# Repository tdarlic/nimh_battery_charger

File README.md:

# NiMh Battery Charger for 4 AA/AAA batteries

Idea taken from BigClive:
[https://www.reddit.com/r/BigCliveDotCom/comments/tcny85/simple_nimh_battery_charger_with_pcb_files/]

In order to know when the batteries might be charged my plan was to use the timer and a LED. 
I need a 24 hour timer and 555 adds more complications and cannot have 24 hours delays.
Then I tried to get a more modern timer solution but at the end it's much cheaper to use cheap MCU.
That seems wastefull to use MCU only as a timer so I'll ad some fluff to it and maybe connect more batteries to one.

For detecting battery and the timers used ch32v003fun:
[https://github.com/cnlohr/ch32v003fun?tab=readme-ov-file]

Example of the dev board:
[https://oshwlab.com/wagiminator/ch32v003f4p6-development-board]

Development board github:
[https://github.com/wuxx/nanoCH32V003]

To use the WCH-LinkE on Linux, you need to grant access permissions beforehand by executing the following commands:

```shell
echo 'SUBSYSTEM=="usb", ATTR{idVendor}=="1a86", ATTR{idProduct}=="8010", MODE="666"' | sudo tee /etc/udev/rules.d/99-WCH-LinkE.rules
echo 'SUBSYSTEM=="usb", ATTR{idVendor}=="1a86", ATTR{idProduct}=="8012", MODE="666"' | sudo tee -a /etc/udev/rules.d/99-WCH-LinkE.rules
sudo udevadm control --reload-rules

```

To upload firmware and perform debugging, you need to ensure that the development board is disconnected from any power sources. Then, you should make the following connections to the WCH-LinkE:
```
| WCH-LinkE |      | DevBoard |
|-----------|------|----------|
|  SWDIO    | <--> |DIO       |
|    3V3    | ---> |3V3       |
|    GND    | ---> |GND       |

```
## NRST [D7] pin AS GPIO
Must be configured to be GPIO and not NRST pin
```shell
./minichlink -D
```
New make command was added to do this
```shell
make nrstoff
```

## Quick reference

## Dev board pinout

## Dev board schematic

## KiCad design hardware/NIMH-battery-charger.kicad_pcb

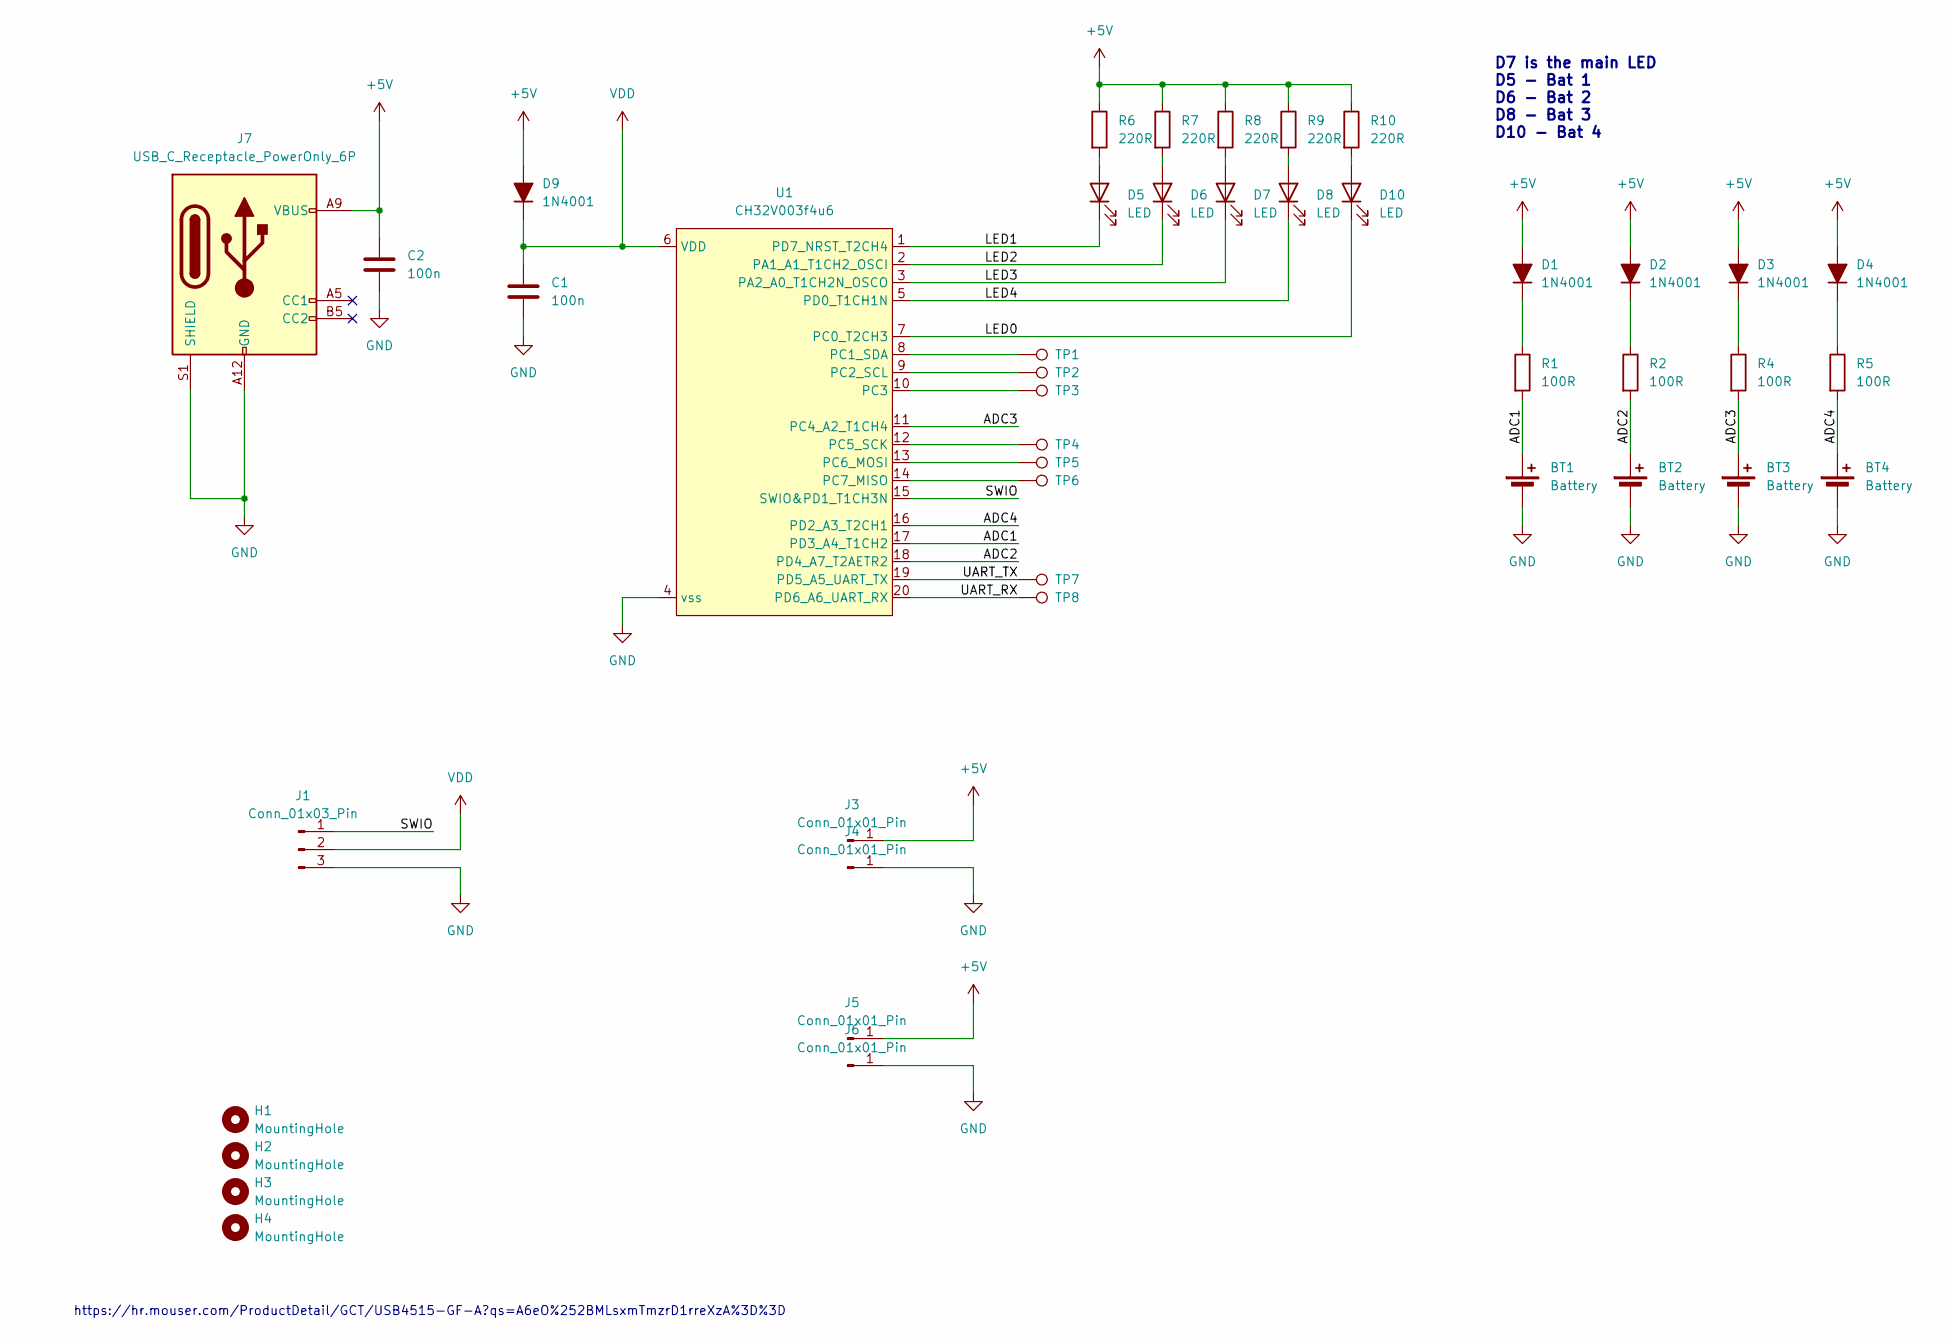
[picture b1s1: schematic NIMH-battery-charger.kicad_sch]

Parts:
BT1, BT2, BT3, BT4: Battery; UM-3X1-AA
C1, C2: 100n; C_0805_2012Metric_Pad1.18x1.45mm
D1, D2, D3, D4, D9: 1N4001; D_SOD-323_BigPads
D5, D6, D7, D8, D10: LED; LED_1206_3216Metric_ReverseMount_Hole1.8x2.4mm
H1, H2, H3, H4: MountingHole; MountingHole_3.2mm_M3_ISO14580_Pad_TopOnly
J1: Conn_01x03_Pin; Harwin_M20-89003xx_1x03_P2.54mm_Horizontal
J3, J4, J5, J6: Conn_01x01_Pin; PAD
J7: USB_C_Receptacle_PowerOnly_6P; USB4515-GF-A
R1, R2, R4, R5: 100R; R_0805_2012Metric_Pad1.20x1.40mm_HandSolder
R6, R7, R8, R9, R10: 220R; R_0805_2012Metric_Pad1.20x1.40mm_HandSolder
TP1, TP2, TP3, TP4, TP5, TP6, TP7, TP8: TestPoint; TestPoint_Pad_D1.5mm
U1: CH32V003f4u6; QFN-20-1EP_3x3mm_P0.4mm_EP1.65x1.65mm

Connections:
+5V: C2.1, D1.2 (A), D2.2 (A), D3.2 (A), D4.2 (A), D9.2 (A), J3.1, J5.1, J7.A9 (VBUS), J7.B9 (VBUS), R6.1, R7.1, R8.1, R9.1, R10.1
/ADC1: BT1.1 (+), R1.2, U1.17 (PD2_A4_T1CH2)
/ADC2: BT2.1 (+), R2.2, U1.18 (PD4_A7_T2AETR2)
/ADC3: BT3.1 (+), R4.2, U1.11 (PC4_A2_T1CH4)
/ADC4: BT4.1 (+), R5.2, U1.16 (PD2_A3_T2CH1)
/LED0: D10.1 (K), U1.7 (PC0_T2CH3)
/LED1: D5.1 (K), U1.1 (PD7_NRST_T2CH4)
/LED2: D6.1 (K), U1.2 (PA1_A1_T1CH2_OSCI)
/LED3: D7.1 (K), U1.3 (PA2_A0_T1CH2N_OSCO)
/LED4: D8.1 (K), U1.5 (PD0_T1CH1N)
/SWIO: J1.1, U1.15 (SWIO&PD1_T1CH3N)
/UART_RX: TP8.1, U1.20 (PD6_A6_UART_RX)
/UART_TX: TP7.1, U1.19 (PD5_A5_UART_TX)
GND: BT1.2 (-), BT2.2 (-), BT3.2 (-), BT4.2 (-), C1.2, C2.2, J1.3, J4.1, J6.1, J7.A12 (GND), J7.B12 (GND), J7.S1 (SHIELD), U1.4 (vss)
unnamed: D1.1 (K), R1.1
unnamed: D2.1 (K), R2.1
unnamed: D3.1 (K), R4.1
unnamed: D4.1 (K), R5.1
unnamed: D5.2 (A), R6.2
unnamed: D6.2 (A), R7.2
unnamed: D7.2 (A), R8.2
unnamed: D8.2 (A), R9.2
unnamed: D10.2 (A), R10.2
unnamed: TP1.1, U1.8 (PC1_SDA)
unnamed: TP2.1, U1.9 (PC2_SCL)
unnamed: TP3.1, U1.10 (PC3)
unnamed: TP4.1, U1.12 (PC5_SCK)
unnamed: TP5.1, U1.13 (PC6_MOSI)
unnamed: TP6.1, U1.14 (PC7_MISO)
VDD: C1.1, D9.1 (K), J1.2, U1.6 (VDD)

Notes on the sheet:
D7 is the main LED D5 - Bat 1 D6 - Bat 2 D8 - Bat 3 D10 - Bat 4
https://hr.mouser.com/ProductDetail/GCT/USB4515-GF-A?qs=A6eO%252BMLsxmTmzrD1rreXzA%3D%3D

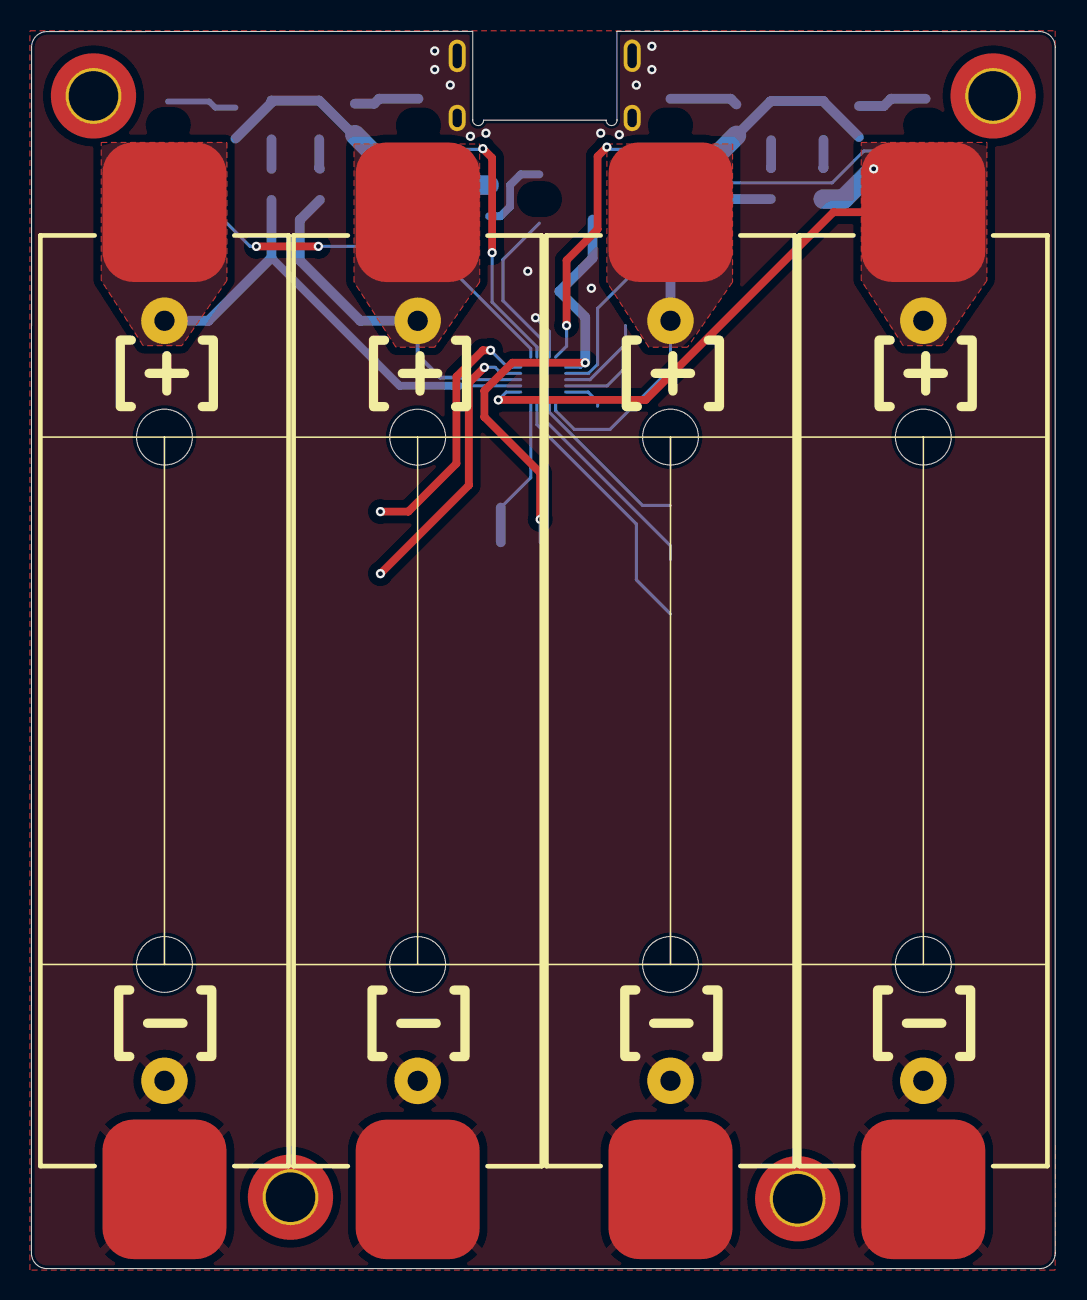
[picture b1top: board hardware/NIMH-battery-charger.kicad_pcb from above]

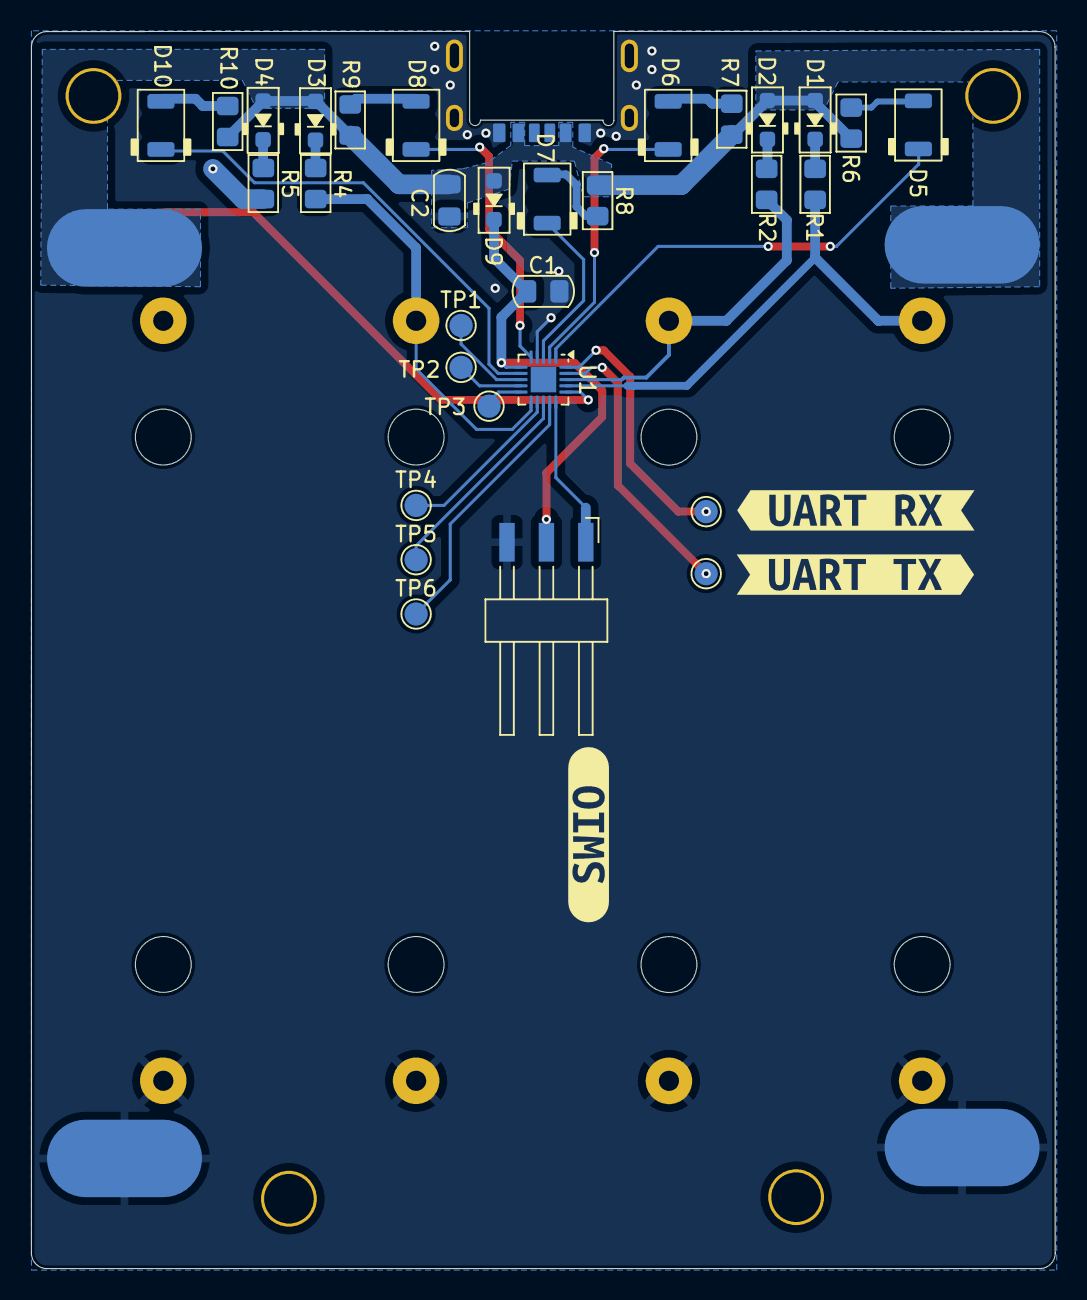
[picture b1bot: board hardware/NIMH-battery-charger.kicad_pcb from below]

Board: 2 copper layers, 66.0 x 79.8 mm, 47 parts (39 on the bottom side), 30 nets.

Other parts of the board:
kibuzzard-672F425B: G***; kibuzzard-672F425B
kibuzzard-672F427A: G***; kibuzzard-672F427A
kibuzzard-672F4251: G***; kibuzzard-672F4251

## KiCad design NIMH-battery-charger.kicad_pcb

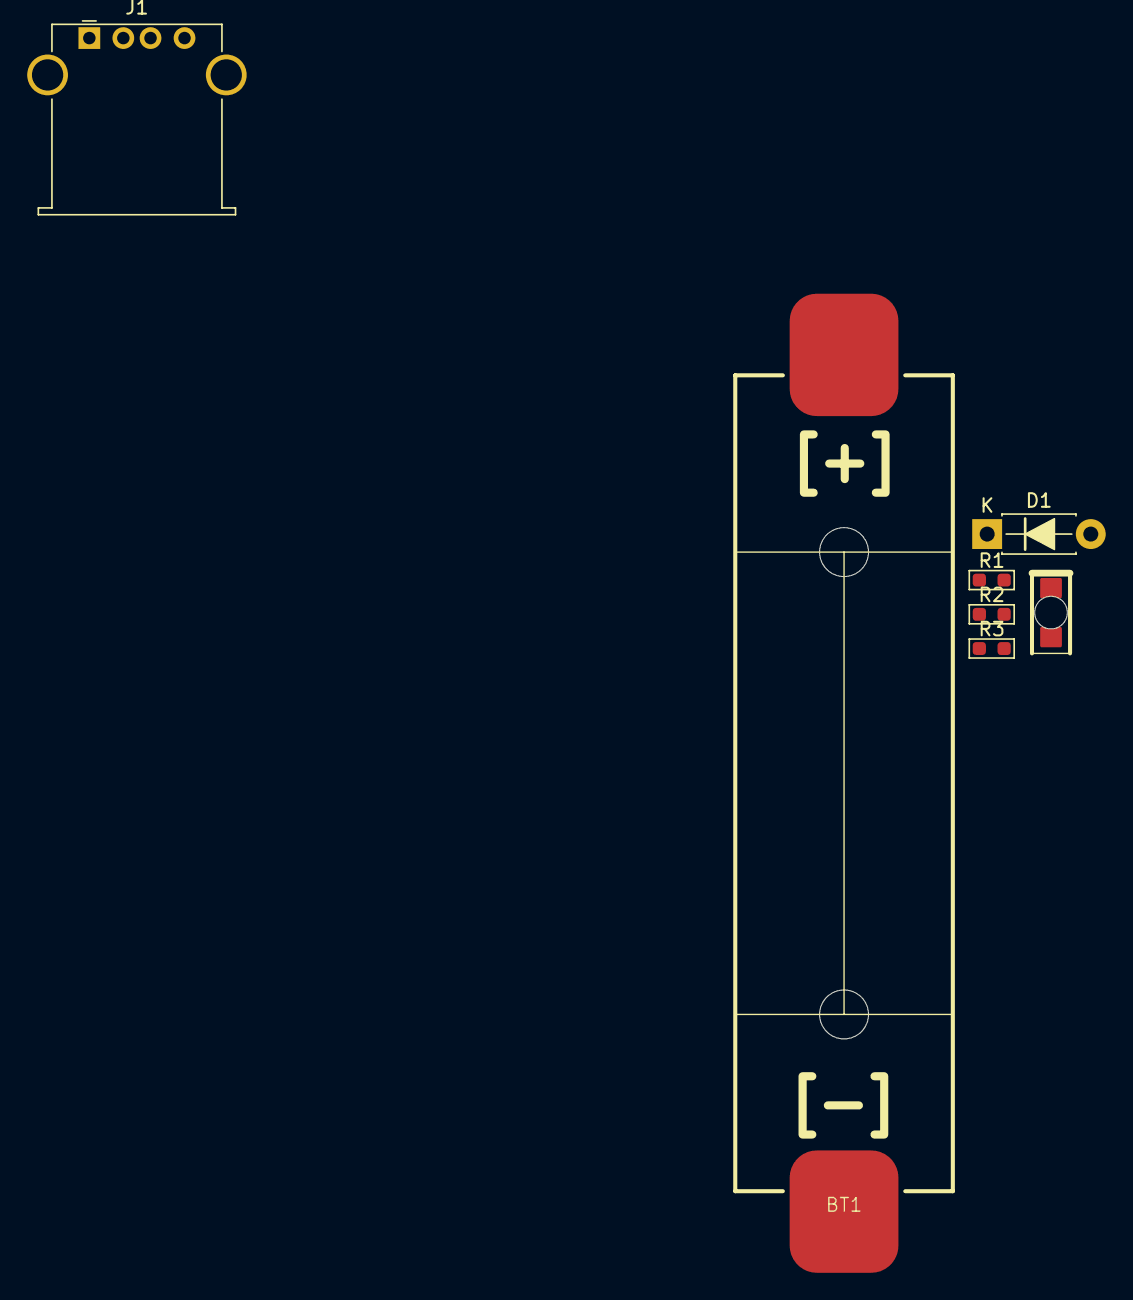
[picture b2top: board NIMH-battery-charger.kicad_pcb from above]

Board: 2 copper layers, 7 parts (0 on the bottom side), 6 nets, no tracks yet.

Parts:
BT1: Battery_Cell; UM-3X1-AA
D1: 1N4001; D_DO-41_SOD81_P7.62mm_Horizontal
D2: LED; KPTR-3216SGC
J1: USB_A; USB_A_Stewart_SS-52100-001_Horizontal
R1, R2: 120R; R_0603_1608Metric_Pad0.98x0.95mm_HandSolder
R3: 0R; R_0603_1608Metric_Pad0.98x0.95mm_HandSolder

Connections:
+5V: D1.2 (A), J1.1 (VBUS)
GND: BT1.2 (-), J1.4 (GND), R3.2
unnamed: BT1.1 (+), R1.2, R2.2
unnamed: D1.1 (K), D2.2 (A), R1.1
unnamed: D2.1 (K), R2.1
unnamed: J1.5 (Shield), R3.1

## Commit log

2024-11-04 Add gitignore
2024-11-04 Removed backup files
2024-11-04 Add CH32 data, move PCB to hardware folder
2024-11-04 Moved pdf to documents folder
2024-11-04 Add auto_saved_files into subdir hardware
2024-11-04 Add readme and some comments
2024-11-04 Add pinout in png
2024-11-04 Correct gitignore reference to auto_saved_files
2024-11-04 Fix auto_saved_files again
2024-11-04 Adding ch32v003fun submodule
2024-11-05 Add comments for development board
2024-11-05 Add more references to README
2024-11-05 Add comment to README
2024-11-05 Correct typo in README
2024-11-05 Completing schematic and adding comments and images
2024-11-07 Add USB_C receptacle
    Add documents
    Resizing the board
2024-11-07 Add leds
2024-11-07 Moving Leds
2024-11-07 Placed all components on board
    Finalizing PCB
    Add all components and place them for routing
2024-11-07 Adding soild GND connection to some pins of USB connector
2024-11-07 Add dimensions and created first gerbers
2024-11-07 Fix number of batteries in readme
2024-11-08 Started routing board
2024-11-09 Completed routing board
    Created gergers for JLCPCB
    Added mounting holes
2024-11-28 Adding first test files from CH32V003FUN
    blink test is copied and sucessfully compiled and flashed
2024-11-29 Removed other pins from blink example
2024-11-29 Got the ADC working sucessfully
    Add better schematic for nanoCH32V003
2024-11-29 Adding build path to gitignore
2024-11-29 Add tests and ceedling conf file
2024-11-29 Simplify makefile
    Makefile was just copied form ch32v003fun and removed some unused
    sections
2024-11-29 Add source tracking to build so it does not rebuild unnecessary files
2024-11-29 Remove tracking changed files with .2024-11-29
    This creates artefacts in ../ch32v003fun so I removed it
2024-11-29 Add nicer PWM value calculation function
2024-11-30 Rename source file made for the nanoCH32V003 board
2024-12-01 Corrected the clock with FUNCONF_SYSTICK_USE_HCLK
2024-12-01 Added comments on LED placement on PCB
    Changed nanoCH32V003 code to print ADC immediately after start
2024-12-07 Add larger holes for the battery holder
2024-12-12 Add separte folders for main and devboard code
    Add comments to hardware
2024-12-14 Fix GPIO status for on off and fix pin1 D7 set as GPIO not nRST
2024-12-17 Add working charging indicator for 24 hours
2024-12-17 Remove debug print lines
2024-12-17 Add configuration to stop debug printf
2024-12-31 Adding comment to change the resistors
2025-01-02 Add comments on measured charging current
2025-04-07 Configure NRST as GPIO
    Added comment to configure NRST [D7] pin as GPIO
    Each new chip needs to be configured with this otherwise LED1 will not
    work
    Removed some unnecessary variables
2025-04-07 Add new make command nrst off to readme
